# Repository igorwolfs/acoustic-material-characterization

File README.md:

# acoustic-emissions-hw
Repository for my non-destructive mechanical measurement device.

## Project Goal
Being able to measure cracks and holes in welds and solid materials by measuring mechanical wave behavior in the material.

## Description
The project will consist of 3 boards
- acoustic-processing-hw (The compute-module)
- acoustic-preamp-hw (The preamp-module)
- acoustic-piezodriver-hw (The driver-module)

## The electronics demistified

The **compute**-module will drive a PWM signal to the **driver**-module. The **driver** contains various DC-DC converters, along with a single-phase inverter. 

The inverter-output is connected to a piezo-element, driving the piezo-element with a 0.1 MHz - 10 MHz block-wave at an amplitude of 40 V, and currents up to 3 A RMS. Optional piezo-specific band-pass filters might be integrated.

The "transmitting" piezo-element and "receiving" piezo-element are connected to the **preamp** board, capable of
- Measuring transmitted power through the sending piezo.
- Measuring reflections back into the sending piezo (due to e.g.: mechanical impedance discontinuities between sending and receiving piezo).
- Measuring received power at the receiving piezo.

The **preamp** board will likely be covering only part of the 0.1-10 MHz frequency band. After some active filtering on the **preamp**-board, the signal is passed onto the front-end present on the **processing**-board. The **processing** board buffers the signal coming from the **preamp** and samples it with 10-bit accuracy at maximum 35 MHz.

## The mechanics demistified
#### Initial piezo-choice
The initial test-piezo used is the [UB161M7](https://www.mouser.de/datasheet/2/334/UB161M7-953231.pdf), which has a resonance frequency of 1.70 MHz.

#### Isotropic behavior
In order to get the best possible results, in terms of wave propagation insights and material properties. Ideally isotropic materials are used. Anisotropic materials will likely require lots of calibration and specific digital processing.

#### Piezo resonance frequency
In order to pass on vibration from the piezo onto the material, it's imperative to match their acoustic impedances. This will likely dampen the resonance curve, and shift the resonance frequency of the piezo.

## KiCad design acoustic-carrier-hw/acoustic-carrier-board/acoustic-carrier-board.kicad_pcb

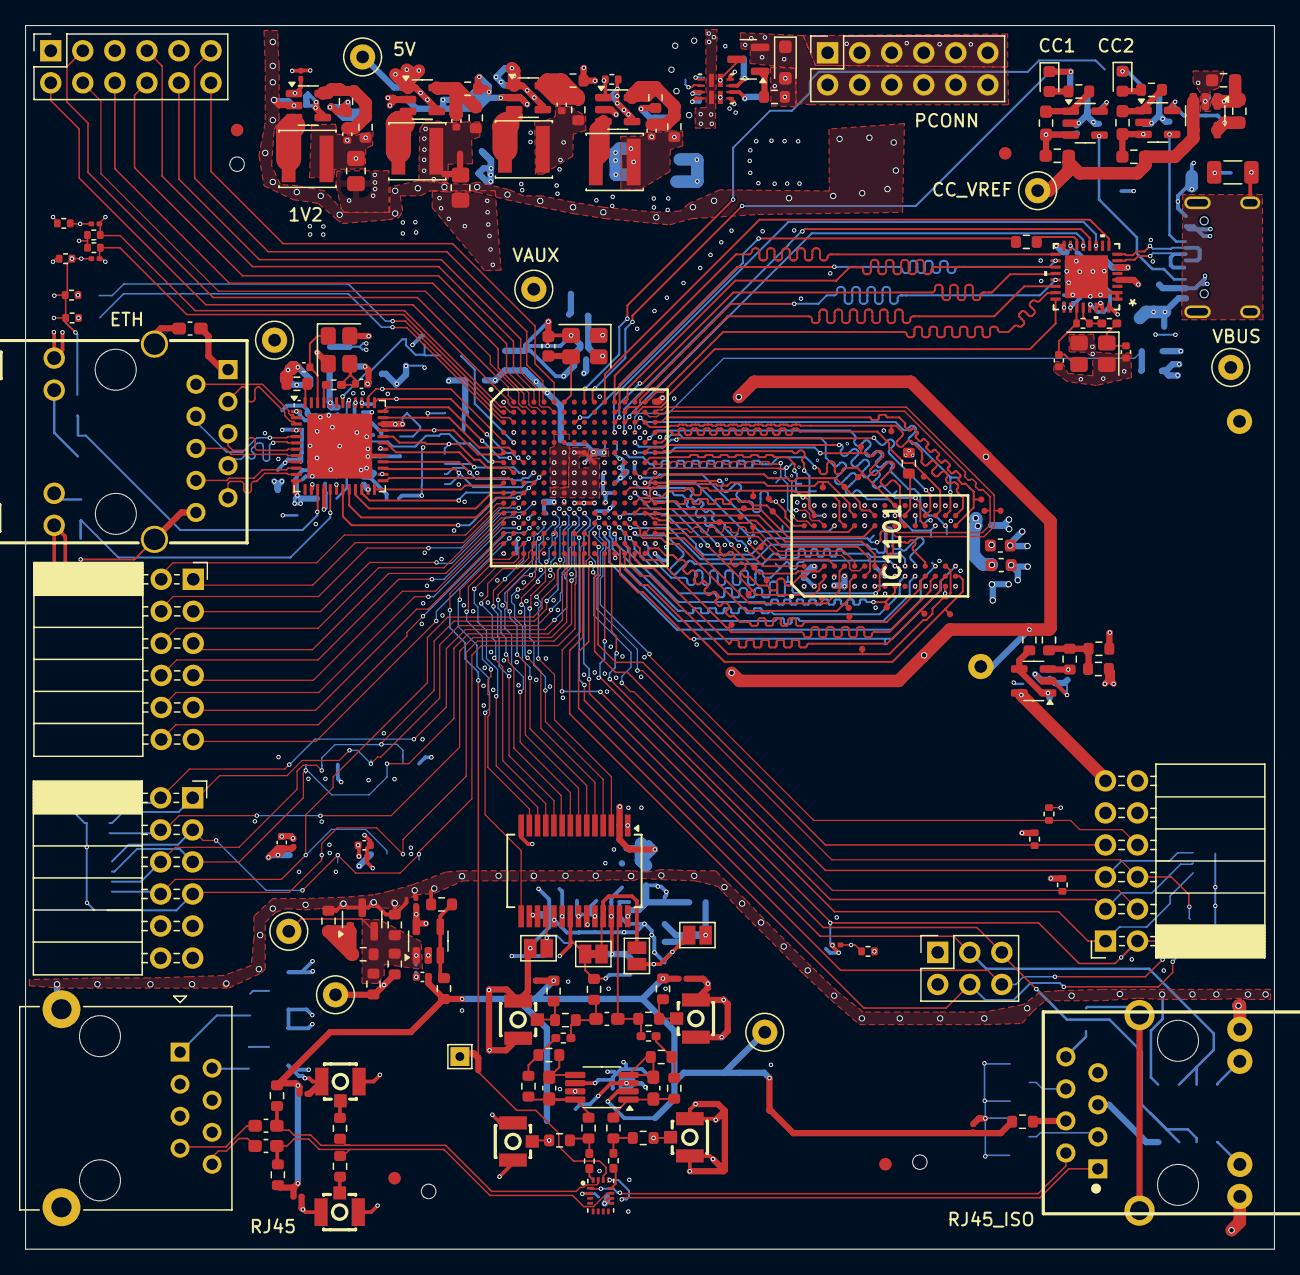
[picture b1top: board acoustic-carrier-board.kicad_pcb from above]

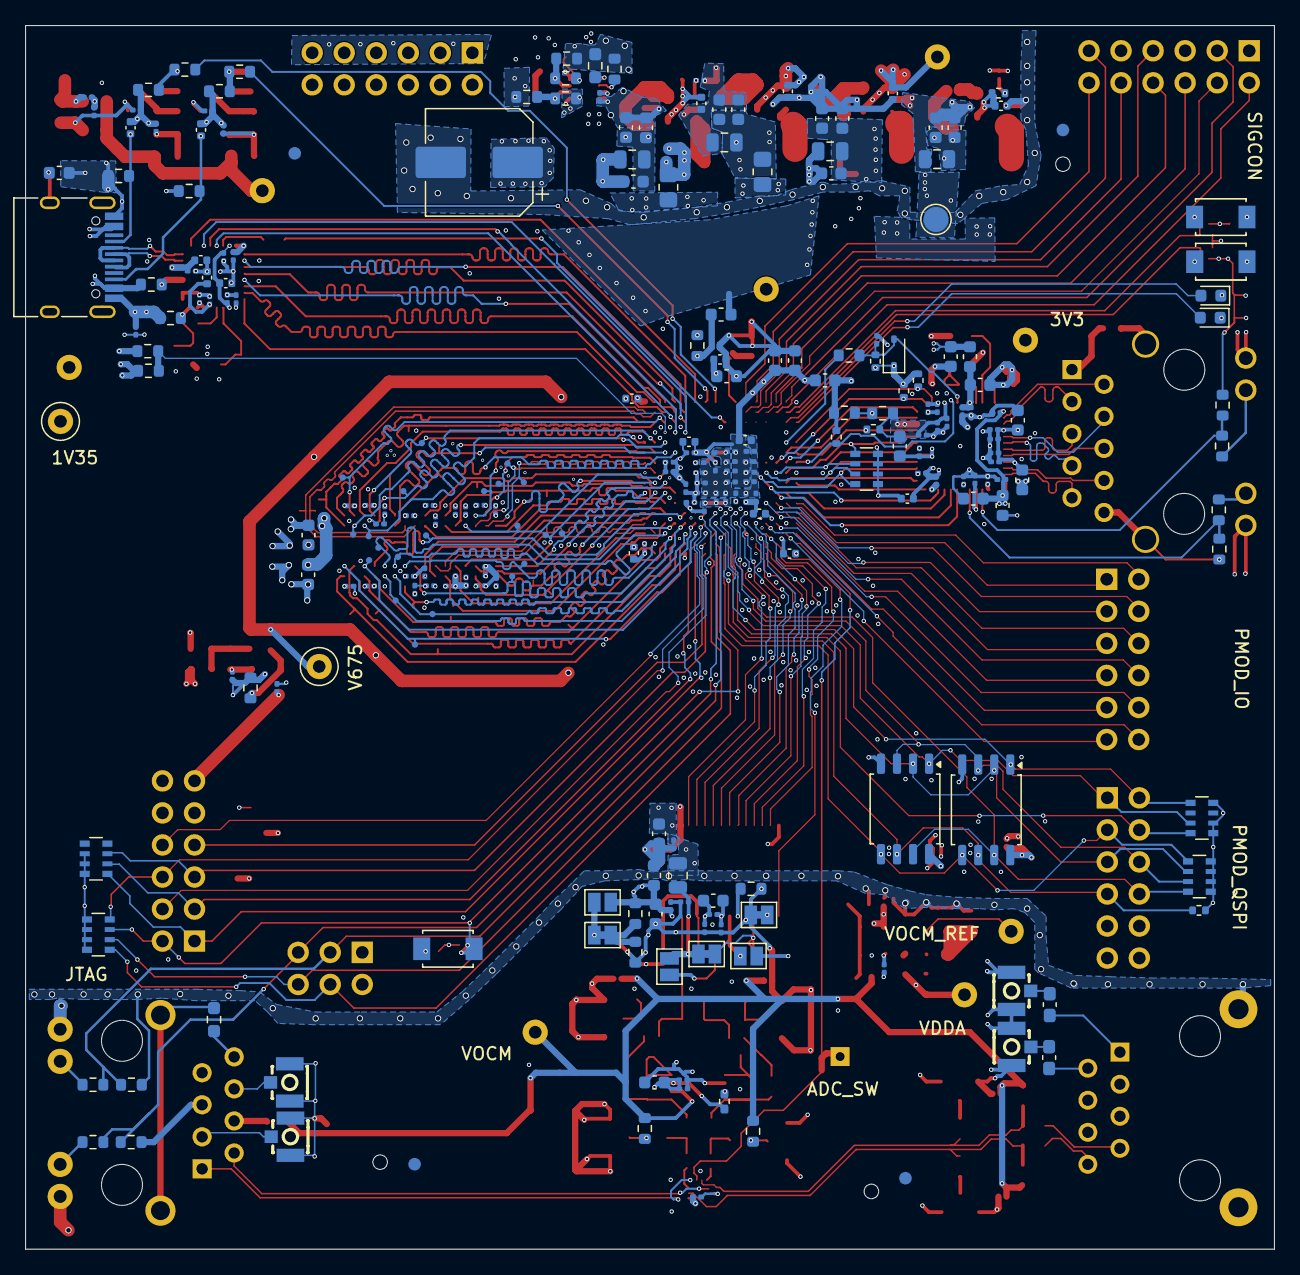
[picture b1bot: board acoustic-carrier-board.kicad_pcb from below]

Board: 6 copper layers, 99.0 x 97.0 mm, 445 parts (250 on the bottom side), 278 nets.

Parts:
C201: 150uF; CP_Elec_8x6.2
C202, C225, C227, C228, C301, C302, C303, C304, C305, C306, C310, C311, C401, C402, C404, C405, C407, C501, C502, C508, C509, C510, C513, C601, C604, C606, C612, C613, C702, C704, C706, C708, C801, C807, C808, C809, C810, C811, C812, C816, C820, C821, C822, C1002, C1003, C1004, C1005, C1008, C1009, C1010, C1011, C1013, C1019, C1021, C1024, C1026, C1027, C1101, C1102, C1103, C1104, C1105, C1106, C1108, C1109, C1110, C1111, C1112, C1116, C1118, C1119, C1120, C1121, C1122, C1123, C1124, C1125, C1203, C1204, C1206, C1207, C1209, C1210, C1216, C1217, C1218, C1219, C1220, C1221, C1222, C1223, C1229: 0.1uF; C_0201_0603Metric
C203, C209, C217, C219: 10pF; C_0402_1005Metric
C204, C205, C206, C210, C211, C214, C215, C220, C221, C222, C307, C308, C309, C1001, C1006, C1007, C1023, C1202, C1205, C1208, C1215, C1224: 10uF; C_0603_1608Metric
C207, C212, C216, C223, C1014: 1uF; C_0805_2012Metric
C208, C213, C218, C224, C312, C403, C406, C503, C512, C603, C611, C701, C705, C707, C813, C814, C819: 4.7uF; C_0402_1005Metric
C226, C507, C511, C602, C703, C802, C817, C825, C1022, C1025, C1114, C1115, C1211, C1212, C1213, C1214, C1225: 10nF; C_0201_0603Metric
C313, C1107, C1113: 22uF; C_0603_1608Metric
C408: 5pF; C_0603_1608Metric
C803, C806, C1227, C1228: 22pF; C_0402_1005Metric
C804, C805: 220pF; C_0402_1005Metric
C815: 1nF; C_1206_3216Metric
C1012, C1015, C1016: 10pF; C_0603_1608Metric_Pad1.08x0.95mm_HandSolder
C1017, C1018, C1028, C1029, C1226: 100 nF +-5%; C_0603_1608Metric_Pad1.08x0.95mm_HandSolder
C1020: 220nF; C_0402_1005Metric
D201: D_Zener; D_SOD-323_HandSoldering
D601, D602, D801, D802: LED_RED; LED_0603_1608Metric
D1201: 1N4148WS; D_SOD-323
FID101, FID102, FID103, FID104, FID105, FID106, FID107, FID108: Fiducial; Fiducial_1mm_Mask2mm
H101, H102, H103: MountingHole; ToolingHole_1.152mm
IC1: ECP5-BGA256; BGA256C80P16X16_1400X1400X170
IC1101: MT41K256M16TW-107_P; BGA96C80P9X16_800X1400X120
J201, J903: Conn_02x06_Odd_Even; PinSocket_2x06_P2.54mm_Vertical
J701: Conn_02x03_Odd_Even; PinSocket_2x03_P2.54mm_Vertical
J702: PMOD_JTAG; PMOD_Pinsocket
J703: PMOD_SPI; PMOD_Pinsocket
J704: PMOD_GPIO; PMOD_Pinsocket
J801: TYPE-C-31-M-12; USB_C_Receptacle_HRO_TYPE-C-31-M-12
J1001, J1002, J1003, J1004, J1005, J1006, J1008, J1009, J1010, J1011: BWU.FL-IPEX1
J1007: 8P8C_Shielded; RJ45_RCH_RC01937
J1201: HR911130A; RJ45-TH_HR911130A
JP1001, JP1004, JP1007, JP1008: SolderJumper_2_Bridged; SolderJumper-2_P1.3mm_Bridged_Pad1.0x1.5mm
JP1002, JP1003, JP1005, JP1006, JP1009, JP1010: SolderJumper_2_Open; SolderJumper-2_P1.3mm_Open_Pad1.0x1.5mm
L201, L202, L203, L204: 2.2uH; L_Changjiang_FNR4018S
L401, L801, L1001, L1101, L1102, L1201, L1202, L1203: 120@100MHz; L_0603_1608Metric
Q201: AO3401A; SOT-23
R201, R202, R604, R606, R704, R705, R707, R1204, R1208, R1212, R1213: 4.7k; R_0402_1005Metric
R203, R216, R225, R226: 24k; R_0603_1608Metric
R204, R803, R811: 100k; R_0603_1608Metric_Pad0.98x0.95mm_HandSolder
R205: 27k; R_0603_1608Metric
R206, R212: 22k; R_0603_1608Metric
R207, R227, R804, R805: 5.1k; R_0603_1608Metric
R208, R209, R217, R301: 0; R_0805_2012Metric_Pad1.20x1.40mm_HandSolder
R210, R211, R213: 100k; R_0603_1608Metric
R215: 75k; R_0603_1608Metric
R218: 30k; R_0603_1608Metric
R219, R223, R224, R401, R815, R830, R1009, R1013, R1021, R1024, R1030, R1031, R1032, R1034, R1036, R1037: 1k; R_0603_1608Metric
R220, R221, R602, R817, R1007, R1008, R1011, R1014, R1022, R1025, R1026, R1039, R1043: 0; R_0603_1608Metric
R222, R801: 220; R_0603_1608Metric
R601, R603, R605, R607, R701: 470; R_0402_1005Metric
R706, R1205: 1k; R_0402_1005Metric
R802, R812: 3k9; R_0603_1608Metric_Pad0.98x0.95mm_HandSolder
R806: 1M; R_0402_1005Metric
R807, R1012, R1015, R1017, R1018, R1020, R1201: 0; R_0402_1005Metric_Pad0.72x0.64mm_HandSolder
R808, R1202: 12k+-1%; R_0603_1608Metric
R809, R810: 33k; R_0603_1608Metric
R813, R821, R1016, R1019: 47; R_0603_1608Metric
R814, R826, R1038: 4.7k; R_0603_1608Metric
R816: 56k; R_0603_1608Metric_Pad0.98x0.95mm_HandSolder
R818: 9k1; R_0603_1608Metric_Pad0.98x0.95mm_HandSolder
R1001: 0; R_0603_1608Metric_Pad0.98x0.95mm_HandSolder
R1002, R1003, R1004, R1005, R1206, R1209: 470; R_0603_1608Metric
R1006, R1010, R1023, R1027, R1028, R1029, R1203, R1207, R1210, R1211: 10k; R_0603_1608Metric
R1033: 75; R_0603_1608Metric
R1035: 1k5; R_0603_1608Metric
R1101: 240; R_0603_1608Metric
RJ1001: HR913550A; RJ45-TH_HR913550A
RN703, RN704, RN708, RN1201: 4x4k7; R_Array_Convex_4x0603
RN707: 4x10k; R_Array_Convex_4x0603
SW602, SW603, SW701: SW_Push; SW_TS-1088-AR02016
TP202, TP205, TP207, TP208, TP209, TP210, TP801, TP1001, TP1011, TP1012: TestPoint; TestPoint_Loop_D1.80mm_Drill1.0mm_Beaded
TP206: TestPoint; TestPoint_Pad_D2.0mm
TP1005: TestPoint; TestPoint_THTPad_1.5x1.5mm_Drill0.7mm
TP1101, TP1102, TP1103, TP1104, TP1105, TP1106, TP1107, TP1108, TP1109, TP1110, TP1111, TP1112, TP1113, TP1114, TP1115, TP1116, TP1117, TP1118, TP1119, TP1120, TP1121, TP1122, TP1123, TP1124, TP1125, TP1126, TP1127, TP1128, TP1129, TP1130, TP1131, TP1132, TP1133, TP1134, TP1135, TP1136, TP1137, TP1138, TP1139, TP1140, TP1141, TP1142, TP1143, TP1144, TP1145, TP1146, TP1147, TP1148, TP1149: TestPoint_0.25mm; TestPoint_Pad_D0.25mm
U201: TPS2121RUX; TPS2121
U202, U203, U204, U205: TLV62569DBV; SOT-23-5
U206: OPA376xxDBV; SOT-23-5
U701, U702: W25Q128JVS; SOIC-8_5.3x5.3mm_P1.27mm
U801: USB3300-EZK; QFN32_5X5MC_MCH
U802, U1004: LMV321; SOT-23-5
U803, U804: SOT-23-5
U1001: MS9280; SSOP-28_5.3x10.2mm_P0.65mm
U1002: THS4521IDGK; VSSOP-8_3x3mm_P0.65mm
U1003: DGQ2788AEN-T1-GE4; QFN40P260X180X60-16N_Fv1.2
U1005: TL432DBZ; SOT-23
U1201: KSZ9031RN; QFN-48-1EP_7x7mm_P0.5mm_EP5.15x5.15mm
Y401: Crystal Oscillator; Crystal_SMD_3225-4Pin_3.2x2.5mm
Y801: Crystal_GND24_Small; Crystal_SMD_3225-4Pin_3.2x2.5mm
Y1201: 25MHz; Crystal_SMD_3225-4Pin_3.2x2.5mm

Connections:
+1V2: C209.1, C210.1, C211.1, C212.1, L202.2, R209.1, R211.2
+1V35: C219.1, C220.1, C221.1, C222.1, C223.1, L204.2, R217.1, R218.2
+2V5: C214.1, C215.1, C216.1, C217.1, L203.2, R215.2, R301.1
+3V3: C203.1, C204.1, C205.1, C206.1, C207.1, L201.2, R208.1, R210.2
+5V: C201.1, C208.1, C213.1, C218.1, C224.1, R201.1, R202.1, TP202.1, U201.1 (OUT), U201.8 (OUT), U202.1 (EN), U202.4 (VIN), U203.4 (VIN), U204.1 (EN), U204.4 (VIN), U205.4 (VIN)
/ANALOG-FRONTEND/ADC.CLK: IC1.T2 (PL38D), U1001.15 (CLK)
/ANALOG-FRONTEND/ADC.D0: IC1.M6 (PL47A), U1001.3 (D0)
/ANALOG-FRONTEND/ADC.D1: IC1.P6 (PL47C/LLC_GPLL0T_IN), U1001.4 (D1)
/ANALOG-FRONTEND/ADC.D2: IC1.N6 (PL47B), U1001.5 (D2)
/ANALOG-FRONTEND/ADC.D3: IC1.R5 (PL44A/LDQS44), U1001.6 (D3)
/ANALOG-FRONTEND/ADC.D4: IC1.P5 (PL47D/LLC_GPLL0C_IN), U1001.7 (D4)
/ANALOG-FRONTEND/ADC.D5: IC1.N5 (PL44D), U1001.8 (D5)
/ANALOG-FRONTEND/ADC.D6: IC1.T4 (PL44B/LDQSN44), U1001.9 (D6)
/ANALOG-FRONTEND/ADC.D7: IC1.P4 (PL41A), U1001.10 (D7)
/ANALOG-FRONTEND/ADC.D8: IC1.R4 (PL41C), U1001.11 (D8)
/ANALOG-FRONTEND/ADC.D9: IC1.T3 (PL41D), U1001.12 (D9)
/ANALOG-FRONTEND/ADC.OTR: IC1.R3 (PL41B), U1001.13 (OTR)
/ANALOG-FRONTEND/ADC_AIN+: C1015.2, R1011.1, R1017.2, U1001.27 (AIN)
/ANALOG-FRONTEND/ADC_AIN-: C1015.1, R1014.1, R1020.2, R1022.1
/ANALOG-FRONTEND/ADC_MODE: JP1006.2 (B), JP1008.2 (B), JP1010.2 (B), U1001.23 (MODE)
/ANALOG-FRONTEND/ADC_REFBF: C1001.2, C1002.2, C1004.1, U1001.24 (REFBF)
/ANALOG-FRONTEND/ADC_REFBS: JP1004.1 (A), JP1005.2 (B), U1001.25 (REFBS)
/ANALOG-FRONTEND/ADC_REFSENSE: JP1007.2 (B), JP1009.2 (B), U1001.18 (REFSENSE)
/ANALOG-FRONTEND/ADC_REFTF: C1001.1, C1002.1, C1003.1, U1001.22 (REFTF)
/ANALOG-FRONTEND/ADC_REFTS: JP1002.2 (B), JP1003.2 (B), JP1004.2 (B), R1014.2, U1001.21 (REFTS)
/ANALOG-FRONTEND/ADC_VDDA_2: JP1008.1 (A), R1030.2, R1031.1
/ANALOG-FRONTEND/ADC_VOCM_BUFF: C1009.1, C1010.1, C1011.1, C1020.2, C1026.1, C1027.1, R1006.1, R1010.1, R1023.1, R1027.1, R1028.1, R1029.2, R1033.1, R1039.1, TP1012.1, U1002.2 (V_{OCM})
/ANALOG-FRONTEND/ADC_VOCM_REF: C1022.1, R1032.2, R1034.2, R1035.1, R1037.1, TP1011.1, U1004.1 (+), U1005.2 (K)
/ANALOG-FRONTEND/ADC_VREF: C1013.1, C1014.1, JP1002.1 (A), JP1007.1 (A), U1001.26 (VREF)
/ANALOG-FRONTEND/MAG_ADC_AIN+: RJ1001.2, U1003.1 (NC2)
/ANALOG-FRONTEND/MAG_ADC_AIN-: RJ1001.1, U1003.13 (NC1)
/ANALOG-FRONTEND/RJ45_ADC_AIN+: C1018.2, R1008.1, R1029.1, U1003.15 (NO2)
/ANALOG-FRONTEND/RJ45_ADC_AIN-: C1017.2, R1027.2, R1043.1, U1003.11 (NO1)
/CONNECTORS/PMOD_IO.IO1: IC1.L2 (PL26B/PCLKC6_1), J704.1 (IO1/TMS)
/CONNECTORS/PMOD_IO.IO2: IC1.L4 (PL29C/PL29C), J704.2 (IO2/TDI)
/CONNECTORS/PMOD_IO.IO3: IC1.M2 (PL26D/PCLKC6_0), J704.3 (IO3/TDO)
/CONNECTORS/PMOD_IO.IO4: IC1.N1 (PL32A/LDQS32), J704.4 (IO4/TCK)
/CONNECTORS/PMOD_IO.IO5: IC1.P1 (PL35A), J704.5 (GND)
/CONNECTORS/PMOD_IO.IO6: IC1.P2 (PL32B/LDQSN32), J704.6 (Vcc)
/CONNECTORS/PMOD_IO.IO7: IC1.L1 (PL26A/LDQ32/PCLKT6_1), J704.7 (IO5)
/CONNECTORS/PMOD_IO.IO8: IC1.L3 (PL32C), J704.8 (IO6)
/CONNECTORS/PMOD_IO.IO9: IC1.M1 (PL26C/PCLKT6_0), J704.9 (IO7)
/CONNECTORS/PMOD_IO.IO10: IC1.M3 (PL32D), J704.10 (IO8)
/CONNECTORS/PMOD_IO.IO11: IC1.N3 (PL35D), J704.11 (GND)
/CONNECTORS/PMOD_IO.IO12: IC1.N4 (PL38A/LDQ44), J704.12 (Vcc)
/CONNECTORS/SIGCON.IO1: IC1.B3 (PT4B), J903.2
/CONNECTORS/SIGCON.IO2: IC1.A2 (PT4A), J903.3
/CONNECTORS/SIGCON.IO3: IC1.B4 (PT11B), J903.4
/CONNECTORS/SIGCON.IO4: IC1.A3 (PT6A), J903.6
/CONNECTORS/SIGCON.IO5: IC1.A4 (PT6B), J903.7
/CONNECTORS/SIGCON.IO6: IC1.B5 (PT15B), J903.8
/CONNECTORS/SIGCON.IO7: IC1.B6 (PT22B), J903.10
/CONNECTORS/SIGCON.IO8: IC1.A5 (PT18A), J903.11
/CONNECTORS/SIGCON.IO9: IC1.A6 (PT18B), J903.12
/DDR3/DDR3.A0: IC1.M12 (PR44C), IC1101.N3 (A0), TP1137.1
/DDR3/DDR3.A1: IC1.E16 (PR11D/RDQ8), IC1101.P7 (A1), TP1136.1
/DDR3/DDR3.A2: IC1.P11 (PR47C/LRC_GPLL0T_IN), IC1101.P3 (A2), TP1135.1
/DDR3/DDR3.A3: IC1.T15 (PR38D), IC1101.N2 (A3), TP1134.1
/DDR3/DDR3.A4: IC1.D16 (PR8A/RDQS8), IC1101.P8 (A4), TP1133.1
/DDR3/DDR3.A5: IC1.R14 (PR41B), IC1101.P2 (A5), TP1132.1
/DDR3/DDR3.A6: IC1.C14 (PR2C), IC1101.R8 (A6), TP1131.1
/DDR3/DDR3.A7: IC1.T14 (PR41D), IC1101.R2 (A7), TP1130.1
/DDR3/DDR3.A8: IC1.C15 (PR5B), IC1101.T8 (A8), TP1129.1
/DDR3/DDR3.A9: IC1.R13 (PR41C), IC1101.R3 (A9), TP1128.1
/DDR3/DDR3.A10: IC1.F14 (PR5D), IC1101.L7 (A10/AP), TP1127.1
/DDR3/DDR3.A11: IC1.E15 (PR8B/RDQSN8), IC1101.R7 (A11), TP1126.1
/DDR3/DDR3.A12: IC1.F15 (PR11C), IC1101.N7 (A12/BC#), TP1125.1
/DDR3/DDR3.A13: IC1.R12 (PR44A/RDQS44), IC1101.T3 (A13), TP1102.1
/DDR3/DDR3.A14: IC1.C16 (PR5A), IC1101.T7 (A14), TP1101.1
/DDR3/DDR3.BA0: IC1.N11 (PR47B), IC1101.M2 (BA0), TP1146.1
/DDR3/DDR3.BA1: IC1.E14 (PR5C), IC1101.N8 (BA1), TP1147.1
/DDR3/DDR3.BA2: IC1.N13 (PR38A/RDQ44), IC1101.M3 (BA2), TP1148.1
/DDR3/DDR3.CAS#: IC1.R15 (PR38C), IC1101.K3 (CAS#), TP1145.1
/DDR3/DDR3.CK+: IC1.B16 (PR2A/RDQ8), IC1101.J7 (CK), TP1143.1
/DDR3/DDR3.CK-: IC1.B15 (PR2B/S0_IN), IC1101.K7 (CK#), TP1142.1
/DDR3/DDR3.CKE: IC1.F13 (PR8C), IC1101.K9 (CKE), TP1149.1
/DDR3/DDR3.CS#: IC1.P12 (PR47D/LRC_GPLL0C_IN/RDQ44), IC1101.L2 (CS#), TP1140.1
/DDR3/DDR3.DQ0: IC1.P16 (PR35A), IC1101.E3 (DQ0), TP1103.1
/DDR3/DDR3.DQ1: IC1.L16 (PR26A/PCLKT3_1/RDQ32), IC1101.F7 (DQ1), TP1106.1
/DDR3/DDR3.DQ2: IC1.N14 (PR35D/RDQ32), IC1101.F2 (DQ2), TP1116.1
/DDR3/DDR3.DQ3: IC1.L14 (PR32C), IC1101.F8 (DQ3), TP1117.1
/DDR3/DDR3.DQ4: IC1.M16 (PR26C/PCLKT3_0), IC1101.H3 (DQ4), TP1118.1
/DDR3/DDR3.DQ5: IC1.K13 (PR29A/GR_PCLK3_0), IC1101.H8 (DQ5), TP1119.1
/DDR3/DDR3.DQ6: IC1.M15 (PR26D/PCLKC3_0), IC1101.G2 (DQ6), TP1120.1
/DDR3/DDR3.DQ7: IC1.M14 (PR32D), IC1101.H7 (DQ7), TP1121.1
/DDR3/DDR3.DQ8: IC1.H14 (PR14D), IC1101.D7 (DQ8), TP1114.1
/DDR3/DDR3.DQ9: IC1.K16 (PR23C/PCLKT2_0), IC1101.C3 (DQ9), TP1113.1
/DDR3/DDR3.DQ10: IC1.F16 (PR14A/RDQ20), IC1101.C8 (DQ10), TP1112.1
/DDR3/DDR3.DQ11: IC1.K14 (PR20D/GR_PCLK2_0), IC1101.C2 (DQ11), TP1111.1
/DDR3/DDR3.DQ12: IC1.J16 (PR23A/PCLKT2_1), IC1101.A7 (DQ12), TP1110.1
/DDR3/DDR3.DQ13: IC1.K15 (PR23D/PCLKC2_0/RDQ20), IC1101.A2 (DQ13), TP1115.1
/DDR3/DDR3.DQ14: IC1.G15 (PR14B), IC1101.B8 (DQ14), TP1109.1
/DDR3/DDR3.DQ15: IC1.J14 (PR20C/GR_PCLK2_1), IC1101.A3 (DQ15), TP1108.1
/DDR3/DDR3.LDM: IC1.L15 (PR26B/PCLKC3_1), IC1101.E7 (LDM), TP1124.1
/DDR3/DDR3.LDQS+: IC1.N16 (PR32A/RDQS32), IC1101.F3 (LDQS), TP1123.1
/DDR3/DDR3.LDQS-: IC1.P15 (PR32B/RDQSN32), IC1101.G3 (LDQS#), TP1122.1
/DDR3/DDR3.ODT: IC1.N12 (PR44D), IC1101.K1 (ODT), TP1141.1
/DDR3/DDR3.RAS#: IC1.P13 (PR41A), IC1101.J3 (RAS#), TP1144.1
/DDR3/DDR3.RESET#: IC1.T13 (PR44B/RDQSN44), IC1101.T2 (RESET#), TP1138.1
/DDR3/DDR3.UDM: IC1.J15 (PR23B/PCLKC2_1), IC1101.D3 (UDM), TP1104.1
/DDR3/DDR3.UDQS+: IC1.G16 (PR20A/RDQS20), IC1101.B7 (UDQS#), TP1105.1
/DDR3/DDR3.UDQS-: IC1.H15 (PR20B/RDQSN20), IC1101.C7 (UDQS), TP1107.1
/DDR3/DDR3.WE#: IC1.P14 (PR38B), IC1101.L3 (WE#), TP1139.1
/DDR3/VLPDDR3_CORE: C1101.1, C1103.1, C1104.1, C1105.1, C1106.1, C1107.1, C1118.1, C1119.1, C1120.1, C1124.1, IC1101.B2 (VDD_1), IC1101.D9 (VDD_2), IC1101.G7 (VDD_3), IC1101.K2 (VDD_4), IC1101.K8 (VDD_5), IC1101.N1 (VDD_6), IC1101.N9 (VDD_7), IC1101.R1 (VDD_8), IC1101.R9 (VDD_9), L1101.1
/DDR3/VLPDDR3_DQ: C1102.1, C1108.1, C1109.1, C1110.1, C1111.1, C1112.1, C1113.1, C1116.1, C1123.1, C1125.1, IC1101.A1 (VDDQ_1), IC1101.A8 (VDDQ_2), IC1101.C1 (VDDQ_3), IC1101.C9 (VDDQ_4), IC1101.D2 (VDDQ_5), IC1101.E9 (VDDQ_6), IC1101.F1 (VDDQ_7), IC1101.H2 (VDDQ_8), IC1101.H9 (VDDQ_9), L1102.1
/ETHERNET-PHY/ETH_AC_GND: C1226.1, J1201.1
/ETHERNET-PHY/ETH_GLED_K: J1201.12, R1206.1
/ETHERNET-PHY/ETH_LED_1: R1209.2, R1210.1, U1201.17 (LED1/PHAD0/PME_N1)
/ETHERNET-PHY/ETH_LED_2: R1206.2, R1207.1, U1201.15 (LED2/PHYAD1)
/ETHERNET-PHY/ETH_PHY_A+: J1201.2, U1201.2 (TXRXP_A)
/ETHERNET-PHY/ETH_PHY_A-: J1201.3, U1201.3 (TXRXM_A)
/ETHERNET-PHY/ETH_PHY_B+: J1201.4, U1201.5 (TXRXP_B)
/ETHERNET-PHY/ETH_PHY_B-: J1201.7, U1201.6 (TXRXM_B)
/ETHERNET-PHY/ETH_PHY_C+: J1201.5, U1201.7 (TXRXP_C)
/ETHERNET-PHY/ETH_PHY_C-: J1201.6, U1201.8 (TXRXM_C)
/ETHERNET-PHY/ETH_PHY_D+: J1201.8, U1201.10 (TXRXP_D)
/ETHERNET-PHY/ETH_PHY_D-: J1201.9, U1201.11 (TXRXM_D)
/ETHERNET-PHY/ETH_YLED_K: J1201.13, R1209.1
/ETHERNET-PHY/RGMII_MDIO.CLK: IC1.G2 (PL14B), U1201.36 (MDC)
/ETHERNET-PHY/RGMII_MDIO.DATA: IC1.G3 (PL14C), R1205.1, U1201.37 (MDIO)
/ETHERNET-PHY/RGMII_RX.CLK: IC1.F2 (PL11C), R1203.2, R1211.1, U1201.35 (RX_CLK/PHYAD2)
/ETHERNET-PHY/RGMII_RX.CTL: IC1.F1 (PL14A/LDQ20), R1204.1, U1201.33 (RX_DV/CLK125_EN)
/ETHERNET-PHY/RGMII_RX.D0: IC1.H2 (PL20B/LDQS20), RN1201.1 (R1.1), U1201.32 (RXD0/MODE0)
/ETHERNET-PHY/RGMII_RX.D1: IC1.H3 (PL14D), RN1201.2 (R2.1), U1201.31 (RXD1/MODE1)
/ETHERNET-PHY/RGMII_RX.D2: IC1.H4 (PL17B), RN1201.3 (R3.1), U1201.28 (RXD2/MODE2)
/ETHERNET-PHY/RGMII_RX.D3: IC1.H5 (PL17A), RN1201.4 (R4.1), U1201.27 (RXD3/MODE3)
/ETHERNET-PHY/RGMII_TX.CLK: IC1.J1 (PL23A/PCLKT7_1), U1201.24 (GTX_CLK)
/ETHERNET-PHY/RGMII_TX.CTL: IC1.J2 (PL23B/PCLKC7_1), U1201.25 (TX_EN)
/ETHERNET-PHY/RGMII_TX.D0: IC1.K3 (PL20D), U1201.19 (TXD0)
/ETHERNET-PHY/RGMII_TX.D1: IC1.K2 (PL23D/PCLKC7_0/LDQ20), U1201.20 (TXD1)
/ETHERNET-PHY/RGMII_TX.D2: IC1.K1 (PL23C/PCLKT7_0), U1201.21 (TXD2)
/ETHERNET-PHY/RGMII_TX.D3: IC1.J4 (PL17C), U1201.22 (TXD3)
/ETHERNET-PHY/VDDAH_3V3: C1202.1, C1203.1, C1204.1, L1203.2, U1201.1 (AVDDH), U1201.12 (AVDDH)
/ETHERNET-PHY/VDDAL_1V2: C1208.1, C1209.1, C1210.1, C1211.1, C1212.1, L1201.1, U1201.4 (AVDDL), U1201.9 (AVDDL)
/ETHERNET-PHY/VDDAPLL_1V2: C1205.1, C1206.1, C1207.1, L1202.1, U1201.44 (AVDDL_PLL)
/FPGA-BANK-01/USB.CLK: IC1.C8 (PT35A/PCLKT1_0), R817.2
/FPGA-BANK-01/USB.D0: IC1.B14 (PT67A), U801.24 (DATA0)
/FPGA-BANK-01/USB.D1: IC1.A15 (PT67B), U801.23 (DATA1)
/FPGA-BANK-01/USB.D2: IC1.B13 (PT60A), U801.22 (DATA2)
/FPGA-BANK-01/USB.D3: IC1.A14 (PT65B), U801.21 (DATA3)
/FPGA-BANK-01/USB.D4: IC1.C12 (PT56B), U801.20 (DATA4)
/FPGA-BANK-01/USB.D5: IC1.A13 (PT65A), U801.19 (DATA5)
/FPGA-BANK-01/USB.D6: IC1.B12 (PT56A), U801.18 (DATA6)
/FPGA-BANK-01/USB.D7: IC1.A12 (PT53B), U801.17 (DATA7)
/FPGA-BANK-01/USB.DIR: IC1.D13 (PT62A), U801.12 (DIR)
/FPGA-BANK-01/USB.NXT: IC1.D12 (PT58A), U801.11 (NXT)
/FPGA-BANK-01/USB.RST: IC1.A11 (PT53A), U801.9 (RESET)
/FPGA-BANK-01/USB.STP: IC1.C13 (PT60B), U801.13 (STP)
/FPGA-CONFIG-FLASH/FPGA_CFG0: IC1.N10 (CFG0), J702.10 (IO8), R705.1
/FPGA-CONFIG-FLASH/FPGA_CFG1: IC1.P10 (CFG1), J702.9 (IO7), RN704.4 (R4.1)
/FPGA-CONFIG-FLASH/FPGA_CFG2: IC1.R10 (CFG2), J702.8 (IO6), R707.2
/FPGA-CONFIG-FLASH/FPGA_DONE: IC1.P9 (DONE), J701.6, RN704.2 (R2.1)
/FPGA-CONFIG-FLASH/FPGA_RESETH: C708.1, IC1.R9 (~PROGRAM), J702.7 (IO5), RN704.3 (R3.1), SW701.1
/FPGA-CONFIG-FLASH/JTAG.TCK: IC1.T10 (TCK), J702.4 (IO4/TCK), R704.1
/FPGA-CONFIG-FLASH/JTAG.TDI: IC1.R11 (TDI), J702.2 (IO2/TDI), RN703.2 (R2.1)
/FPGA-CONFIG-FLASH/JTAG.TDO: IC1.M10 (TDO), J702.3 (IO3/TDO), RN703.3 (R3.1)
/FPGA-CONFIG-FLASH/JTAG.TMS: IC1.T11 (TMS), J702.1 (IO1/TMS), RN703.1 (R1.1)
/FPGA-CONFIG-FLASH/QSPI.CSPPIn1: IC1.N8 (~HOLD/DI/BUSY/~CSSPI/PB15A), J703.1 (CSn), RN708.3 (R3.1), U701.1 (~CS)
/FPGA-CONFIG-FLASH/QSPI.CSPPIn2: IC1.M8 (DOUT/~CSO/PB15B), J703.7 (IO1), RN708.1 (R1.1), U702.1 (~CS)
/FPGA-CONFIG-FLASH/QSPI.CSn: IC1.R8 (~CS/~S/PB13A), J703.8 (IO2), RN708.4 (R4.1)
/FPGA-CONFIG-FLASH/QSPI.D0: IC1.T8 (D0/PICO/IO0/PB11B), J703.2 (MOSI/DQ0), RN707.1 (R1.1), U701.5 (DI/IO_{0}), U702.5 (DI/IO_{0})
/FPGA-CONFIG-FLASH/QSPI.D1: IC1.T7 (D1/POCI/IO1/PB11A), J703.3 (MISO/DQ1), RN707.2 (R2.1), U701.2 (DO/IO_{1}), U702.2 (DO/IO_{1})
/FPGA-CONFIG-FLASH/QSPI.D2: IC1.M7 (D2/IO2/PB9B), J703.9 (W/DQ2), RN707.3 (R3.1), U701.3 (~WP/IO_{2}), U702.3 (~WP/IO_{2})
/FPGA-CONFIG-FLASH/QSPI.D3: IC1.N7 (D3/IO3/PB9A), J703.10 (HLD/DQ3), RN707.4 (R4.1), U701.7 (~HOLD/~RESET/IO_{3}), U702.7 (~HOLD/~RESET/IO_{3})
/FPGA-CONFIG-FLASH/QSPI.MCLK: IC1.N9 (MCLK/SCK/CCLK), J703.4 (SCK), R706.2, U701.6 (CLK), U702.6 (CLK)
/FPGA-CONFIG-FLASH/~FPGA_INIT: IC1.T9 (~INIT), J701.4, RN704.1 (R1.1)
/FPGA-DQBANK-67/BUTTON_1: C606.1, IC1.B2 (PL2B), R604.2, SW602.1
/FPGA-DQBANK-67/BUTTON_2: C604.1, IC1.B1 (PL2A/LDQ8), R606.2, SW603.1
/FPGA-DQBANK-67/LED_1: D602.2 (A), IC1.C1 (PL5A)
/FPGA-DQBANK-67/LED_2: D601.2 (A), IC1.C2 (PL5B)
/FPGA-POWER/VAUX: C310.1, C311.1, C312.1, C313.1, IC1.G11 (VCCAUX_1), IC1.L7 (VCCAUX_2), R301.2, TP207.1
/POWER/BP_5V: D201.1 (K), J201.2, J201.4, J201.6, J201.8, J201.10, J201.12, Q201.2 (S)
/POWER/USB_VBUS: C801.1, C807.1, C808.1, C822.1, J801.A4 (VBUS), J801.A9 (VBUS), J801.B4 (VBUS), J801.B9 (VBUS), R226.1, R801.1, R809.1, R816.2, TP210.1, U201.2 (IN2), U802.5 (V+), U803.5 (V+), U804.5 (V+)
/USB-PHY/USBCC_VREF_BUFF: R802.1, R812.1, TP801.1, U802.3 (-), U802.4
/USB-PHY/USB_CC1: C805.1, J801.A5 (CC1), R805.2, U804.4 (-)
/USB-PHY/USB_CC2: C804.1, J801.B5 (CC2), R804.2, U803.4 (-)
/USB-PHY/USB_D+: J801.A6 (DP1), J801.B6 (DP2), U801.7 (DP)
/USB-PHY/USB_D-: J801.A7 (DN1), J801.B7 (DN2), U801.8 (DM)
/USB-PHY/USB_SH: C815.1, J801.S1 (SHIELD), L801.2
/USB-PHY/VDDA_USB1V8: C814.1, C816.1, U801.29 (VDDA1.8)
/USB-PHY/VDD_USB1V8: C819.1, C820.1, C821.1, U801.15 (VDD1.8), U801.26 (VDD1.8)
ETH_REFCLK: IC1.G1 (PL20A/GR_PCLK7_1/LDQSN20), R1213.1, U1201.41 (CLK125_NDO/LED_MODE)
FPGA_ADC_LED0: IC1.M9 (~WRITE/PB18A), J701.5, R1004.2, R1005.2
FPGA_ADC_LED1: IC1.P8 (~CS1/PB13B), J701.3, R1002.2, R1003.1
FPGA_ADC_SW: IC1.R1 (PL35B/VREF1_6), TP1005.1, U1003.14 (IN1-2)
FPGA_CC1: IC1.A10 (PT42B), R814.1
FPGA_CC2: IC1.A9 (PT42A), R826.1
FPGA_USB_SENSE: IC1.D14 (PR2D), R809.2, R810.1
GND: C201.2, C202.2, C204.2, C205.2, C206.2, C207.2, C208.2, C210.2, C211.2, C212.2, C213.2, C214.2, C215.2, C216.2, C218.2, C220.2, C221.2, C222.2, C223.2, C224.2, C225.2, C226.2, C227.2, C228.2, C301.2, C302.2, C303.2, C304.2, C305.2, C306.2, C307.2, C308.2, C309.2, C310.2, C311.2, C312.2, C313.2, C401.2, C402.2, C403.2, C404.2, C405.2, C406.2, C407.2, C408.2, C501.2, C502.2, C503.2, C507.2, C508.2, C509.2, C510.2, C511.2, C512.2, C513.2, C601.2, C602.2, C603.2, C604.2, C606.2, C611.2, C612.2, C613.2, C701.2, C702.2, C703.2, C704.2, C705.2, C706.2, C707.2, C708.2, C801.2, C802.2, C803.1, C804.2, C805.2, C806.1, C807.2, C808.2, C809.2, C810.2, C811.2, C812.2, C813.2, C814.2, C815.2, C816.2, C817.2, C819.2, C820.2, C821.2, C822.2, C825.2, C1003.2, C1004.2, C1005.2, C1006.2, C1007.2, C1008.2, C1009.2, C1010.2, C1011.2, C1013.2, C1014.2, C1019.2, C1020.1, C1021.2, C1022.2, C1023.2, C1024.2, C1025.2, C1026.2, C1027.2, C1101.2, C1102.2, C1103.2, C1104.2, C1105.2, C1106.2, C1107.2, C1108.2, C1109.2, C1110.2, C1111.2, C1112.2, C1113.2, C1114.2, C1115.2, C1116.2, C1118.2, C1119.2, C1120.2, C1121.2, C1122.2, C1123.2, C1124.2, C1125.2, C1202.2, C1203.2, C1204.2, C1205.2, C1206.2, C1207.2, C1208.2, C1209.2, C1210.2, C1211.2, C1212.2, C1213.2, C1214.2, C1215.2, C1216.2, C1217.2, C1218.2, C1219.2, C1220.2, C1221.2, C1222.2, C1223.2, C1224.2, C1225.2, C1226.2, C1227.1, C1228.1, C1229.2, D201.2 (A), IC1.A1 (GND_1), IC1.A16 (GND_2), IC1.D2 (GND_3), IC1.D15 (GND_4), IC1.F8 (GND_5), IC1.F9 (GND_6), IC1.G8 (GND_7), IC1.G10 (GND_8), IC1.H1 (GND_9), IC1.H8 (GND_10), IC1.H9 (GND_11), IC1.H10 (GND_12), IC1.H16 (GND_13), IC1.J8 (GND_14), IC1.J9 (GND_15), IC1.J10 (GND_16), IC1.K6 (GND_17), IC1.K7 (GND_18), IC1.K8 (GND_19), IC1.K9 (GND_20), IC1.K10 (GND_21), IC1.N2 (GND_22), IC1.N15 (GND_23), IC1.T1 (GND_24), IC1.T5 (GND_25), IC1.T12 (GND_26), IC1.T16 (GND_27), IC1101.A9 (VSS_1), IC1101.B1 (VSSQ_1), IC1101.B3 (VSS_2), IC1101.B9 (VSSQ_2), IC1101.D1 (VSSQ_3), IC1101.D8 (VSSQ_4), IC1101.E1 (VSS_3), IC1101.E2 (VSSQ_5), IC1101.E8 (VSSQ_6), IC1101.F9 (VSSQ_7), IC1101.G1 (VSSQ_8), IC1101.G8 (VSS_4), IC1101.G9 (VSSQ_9), IC1101.J2 (VSS_5), IC1101.J8 (VSS_6), IC1101.M1 (VSS_7), IC1101.M9 (VSS_8), IC1101.P1 (VSS_9), IC1101.P9 (VSS_10), IC1101.T1 (VSS_11), IC1101.T9 (VSS_12), J201.1, J201.3, J201.5, J201.7, J201.9, J201.11, J701.1, J702.5 (GND), J702.11 (GND), J703.5 (GND), J703.11 (GND), J801.A1 (GND), J801.A12 (GND), J801.B1 (GND), J801.B12 (GND), J903.1, J903.5, J903.9, J1001.2 (Ext), J1002.2 (Ext), J1003.2 (Ext), J1004.2 (Ext), J1005.2 (Ext), J1006.2 (Ext), J1007.SH, J1008.2 (Ext), J1009.2 (Ext), J1010.2 (Ext), J1011.2 (Ext), J1201.10, J1201.S1 (SHIELD), J1201.S2 (SHIELD), JP1001.1 (A), JP1005.1 (A), JP1009.1 (A), JP1010.1 (A), L801.1, R204.2, R205.1, R206.2, R207.2, R212.1, R213.1, R216.1, R223.2, R224.1, R225.1, R227.2, R601.1, R603.1, R605.2, R607.2, R701.2, R704.2, R705.2, R707.1, R804.1, R805.1, R808.1, R810.2, R815.2, R818.1, R830.2, R1001.1, R1003.2, R1005.1, R1025.1, R1031.2, R1036.1, R1037.2, R1038.2, R1101.2, R1202.2, R1207.2, R1210.2, R1211.2, R1213.2, RJ1001.5, RJ1001.8 (GND), U201.3 (CP2), U201.6 (PR1), U201.12 (GND), U202.2 (GND), U203.2 (GND), U204.2 (GND), U205.2 (GND), U206.2 (V-), U701.4 (GND), U702.4 (GND), U801.1 (GND), U801.2 (GND), U801.33 (EPAD), U802.2 (V-), U803.2 (V-)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
unnamed: C806.2, R807.1, Y801.1
unnamed: C1012.1, R1016.2, U1002.4
unnamed: C1016.2, R1019.2, U1002.5
unnamed: C1017.1, J1007.8
unnamed: C1018.1, J1007.7
unnamed: C1028.1, J1007.1
unnamed: C1029.1, J1007.2
unnamed: C1228.2, R1201.1, Y1201.3
unnamed: D601.1 (K), R601.2
unnamed: D602.1 (K), R603.2
unnamed: D801.2 (A), R813.1
unnamed: D801.1 (K), R814.2, R815.1
unnamed: D802.2 (A), R821.1
unnamed: D802.1 (K), R826.2, R830.1
unnamed: C408.1, IC1.A7 (PT29A/PCLKT0_0), Y401.3 (OUT)
unnamed: IC1.E2 (PL8B/LDQSN8), R602.1
unnamed: IC1101.L8 (ZQ), R1101.1
unnamed: J1001.1 (In), R1006.2, R1007.1
unnamed: J1002.1 (In), R1010.2, R1011.2
unnamed: J1003.1 (In), R1008.2
unnamed: C1029.2, J1004.1 (In)
unnamed: J1005.1 (In), R1043.2
unnamed: J1006.1 (In), R1022.2, R1023.2
unnamed: J1008.1 (In), R1026.2, R1028.2
unnamed: J1009.1 (In), RJ1001.3
unnamed: J1010.1 (In), RJ1001.6
unnamed: C1028.2, J1011.1 (In)
unnamed: JP1001.2 (B), U1001.16 (TRISTATE), U1001.17 (STBY)
unnamed: Q201.3 (D), R203.1, U201.7 (IN1)
unnamed: Q201.1 (G), R206.1
unnamed: R219.2, R220.1, R221.2, R223.1
unnamed: R605.1, SW602.2
unnamed: R607.1, SW603.2
unnamed: R701.1, SW701.2
unnamed: R1001.2, RJ1001.13, RJ1001.14
unnamed: R1002.1, RJ1001.11
unnamed: R1004.1, RJ1001.10
unnamed: R1007.2, R1012.2, R1013.2
unnamed: R1009.1, R1016.1, R1017.1
unnamed: R1018.2, R1021.2, R1026.1
unnamed: R1019.1, R1020.1, R1024.2
unnamed: R1039.2, RJ1001.4
unnamed: R205.2, U201.10 (ILM)
unnamed: R203.2, R207.1, U201.5 (OV1)
unnamed: R226.2, R227.1, U201.4 (OV2)
unnamed: C202.1, U201.11 (SS)
unnamed: R204.1, U201.9 (ST)
unnamed: C203.2, R210.1, R212.2, U202.5 (FB)
unnamed: L201.1, U202.3 (SW)
unnamed: C228.1, R201.2, U203.1 (EN)
unnamed: C209.2, R211.1, R213.2, U203.5 (FB)
unnamed: L202.1, U203.3 (SW)
unnamed: C217.2, R215.1, R216.2, U204.5 (FB)
unnamed: L203.1, U204.3 (SW)
unnamed: C227.1, R202.2, U205.1 (EN)
unnamed: C219.2, R218.1, R225.2, U205.5 (FB)
unnamed: L204.1, U205.3 (SW)
unnamed: C226.1, R221.1, U206.3 (+)
unnamed: R222.2, R224.2, U206.1, U206.4 (-)
unnamed: R817.1, U801.14 (CLKOUT)
unnamed: R808.2, U801.32 (RBIAS)
unnamed: R801.2, U801.4 (VBUS)
unnamed: R806.1, R807.2, U801.28 (XI)
unnamed: C803.2, R806.2, U801.27 (XO), Y801.3
unnamed: C802.1, R816.1, R818.2, U802.1 (+)
unnamed: C817.1, R811.1, R812.2, U803.3 (+)
unnamed: R811.2, R813.2, U803.1 (OUT)
unnamed: C825.1, R802.2, R803.1, U804.3 (+)
unnamed: R803.2, R821.2, U804.1 (OUT)
unnamed: R1025.2, U1001.20 (CLAMPIN)
unnamed: C1016.1, R1021.1, R1024.1, U1002.8 (+)
unnamed: C1012.2, R1009.2, R1013.1, U1002.1 (-)
unnamed: R1015.2, U1002.7 (~PD)
unnamed: R1012.1, U1003.12 (COM1)
unnamed: R1018.1, U1003.16 (COM2)
unnamed: R1033.2, R1036.2, U1004.3 (-), U1004.4
unnamed: R1035.2, R1038.1, U1005.1 (REF)
unnamed: R1202.1, U1201.48 (ISET)
unnamed: C1227.2, U1201.46 (XI), Y1201.1
unnamed: R1201.2, U1201.45 (XO)
unnamed: R401.2, Y401.1 (Tri-State)
unnamed: C407.1, L401.2, R401.1, Y401.4 (VDD)
VCORE_3V3: C225.1, C301.1, C302.1, C303.1, C304.1, C305.1, C306.1, C307.1, C308.1, C309.1, C401.1, C402.1, C403.1, C404.1, C405.1, C406.1, C601.1, C602.1, C603.1, C611.1, C612.1, C613.1, C701.1, C702.1, C703.1, C704.1, C705.1, C706.1, C707.1, C809.1, C810.1, C811.1, C812.1, C813.1, C1007.1, C1008.1, C1221.1, C1222.1, C1223.1, C1224.1, C1225.1, D1201.1 (K), IC1.F6 (VCCIO0_1), IC1.F7 (VCCIO0_2), IC1.F10 (VCCIO1_1), IC1.F11 (VCCIO1_2), IC1.G6 (VCC_1), IC1.G7 (VCC_2), IC1.G9 (VCC_3), IC1.H6 (VCCIO7_1), IC1.H7 (VCCIO7_2), IC1.J6 (VCCIO6_1), IC1.J7 (VCCIO6_2), IC1.L6 (VCCIO8), IC1.L8 (VCC_4), IC1.L9 (VCC_5), IC1.L10 (VCC_6), J701.2, J702.6 (Vcc), J702.12 (Vcc), J703.6 (Vcc), J703.12 (Vcc), J1201.11, J1201.14, L401.1, L1001.1, L1203.1, R208.2, R604.1, R606.1, R706.1, R1203.1, R1204.2, R1205.2, R1208.2, R1212.2, RN703.6 (R3.2), RN703.7 (R2.2), RN703.8 (R1.2), RN704.5 (R4.2), RN704.6 (R3.2), RN704.7 (R2.2), RN704.8 (R1.2), RN707.5 (R4.2), RN707.6 (R3.2), RN707.7 (R2.2), RN707.8 (R1.2), RN708.5 (R4.2), RN708.6 (R3.2), RN708.8 (R1.2), RN1201.5 (R4.2), RN1201.6 (R3.2), RN1201.7 (R2.2), RN1201.8 (R1.2), TP205.1, U206.5 (V+), U701.8 (VCC), U702.8 (VCC), U801.6 (VDD3.3), U801.16 (VDD3.3), U801.25 (VDD3.3), U801.30 (VDD3.3), U801.31 (REG_EN), U1001.2 (DRVDD), U1201.16 (DVDDH), U1201.34 (DVDDH), U1201.40 (DVDDH)
VDDA: C1005.1, C1006.1, C1019.1, C1021.1, C1023.1, C1024.1, C1025.1, JP1003.1 (A), JP1006.1 (A), L1001.2, R1015.1, R1030.1, R1032.1, R1034.1, RJ1001.9, RJ1001.12, TP1001.1, U1001.28 (AVDD), U1002.3 (V_{S+}), U1003.10 (V+), U1004.5 (V+)
VETH_1V2: C1213.1, C1214.1, C1215.1, C1216.1, C1217.1, C1218.1, C1219.1, C1220.1, L1201.2, L1202.2, R209.2, TP206.1, U1201.14 (DVDDL), U1201.18 (DVDDL), U1201.23 (DVDDL), U1201.26 (DVDDL), U1201.30 (DVDDL), U1201.39 (DVDDL)
VLPDDR3_1V35: C501.1, C502.1, C503.1, C509.1, C510.1, C511.1, C512.1, IC1.H11 (VCCIO2_1), IC1.J11 (VCCIO2_2), IC1.K11 (VCCIO3_1), IC1.L11 (VCCIO3_2), L1101.2, L1102.2, R217.2, R219.1, TP209.1
VLPDDR3_V675: C507.1, C508.1, C513.1, C1114.1, C1115.1, C1121.1, C1122.1, IC1.G14 (PR14C/VREF1_2), IC1.R16 (PR35B/VREF1_3), IC1101.H1 (VREFDQ), IC1101.M8 (VREFCA), R220.2, R222.1, TP208.1
~ETH_INT: IC1.E1 (PL11D/LDQ8), R1208.1, U1201.38 (INT_N/PME_N2)
~ETH_RESET: C1229.1, D1201.2 (A), R602.2, R1212.1, U1201.42 (RESET_N)

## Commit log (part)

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2025-04-27 [simulations] Added vishay FET to inverter bridge + connected Vs [documentation] Redid driving circuitry calculation [next] Spot a decent ADC
2025-04-27 [simulations] Updated sim with new values [kicad] Added inverter circuitry to schematic, add bulk capacitor LCSC parts, add pads for power connections.
2025-04-28 [kicad] Added capacitors, [documentation] Added bootstrap + HF frequency capacitor calculations
2025-04-29 [kicad] Added analog front-end schematic and MS9280 symbol
2025-04-29 [documentation, kicad] Added decoupling capacitors + input circuitry for adc (next) Look for a decent connector
2025-04-30 [documentation] Researched output power connectors and input connectors (next) select appropriate terminal and rj45 connector
2025-05-01 [kicad] Added connector + input circuit (next) Simulate adc input circuit in ltspice
2025-05-01 [simulations] Finished full adc input stage simulation
2025-05-02 [documentation] Added info on example circuits used, worked on filtering and FPGA info
2025-05-02 [VHDL]added VHDL folder
2025-05-03 [simulations] Added comments concerning differential vs single-ended filtering
2025-05-03 [VHDL] Added initial verilog examples + extra FPGA choices
2025-05-03 [VHDL, lit3rick example] Finished going over example vhdl
2025-05-04 [VHDL] (examples) Went over examples to check global data-flow
2025-05-04 [documentation] Minor changes in docs
2025-05-04 [kicad] Added flash memory + flash connection (next) Add RAM and ethernet
2025-05-06 [kicad] Connected DDR3L bus, added info on FPGA and ddr pin functionality (next) add filtering circuitry for DDR power pins
2025-05-06 [kicad] re-added passive values after accidental removal
2025-05-06 [simulations] Added 3 buck converter simulations (next) Add fast-switching 13 V buck converter simulation + try improving the switching regulator characteristics with extra 10 uF cap
2025-05-06 [kicad] Added switching regulators for 3.3, 1.25 and 2.5
2025-05-07 [general] Major repo reorganization, separated into carrier-board, power-board, preamp-board
2025-05-07 test
2025-05-08 [carrier] Same as previous [piezodriver] Moved inverter to separate board
2025-05-08 [carrier] Added decoupling for DDR (next) Finish power supply
2025-05-08 added decoupling and power flags
2025-05-09 [carrier] Added space for ferrite bead in between bulk and decoupling caps
2025-05-10 [carrier] Finished ethernet
2025-05-10 [carrier] Added usb power + communication circuitry (next) Connect ADC pins to bank 0, select PWM pins, check connectors for power board
2025-05-11 [carrier] Added adc connections and PWM + poweer connectors
2025-05-11 [piezodriver] Added piezo-driver board connectors
2025-05-12 [piezo-driver] Doing boost converter simulations (next) fix weird transient, add buck-converter simulations for 10 and 5 V
2025-05-13 [piezodriver] Fixed the basic boost converter simualtion
2025-05-14 [piezodriver] (simulations) figured minimum driving voltage for FET is > 4 V (next) Add Sepic, check behavior > 7.2 V
2025-05-14 [piezodriver] Selection of diode and fet (next) do SEPIC calculations
2025-05-18 [piezodriver] Added notes on sepic calculation
2025-05-18 [piezodriver] Did analysis of SEPIC, went over inherent duty cycle limits, losses, slope compensation, sense resistor and peak current control
2025-05-18 [piezodriver] (ltspice) Added dead-time to full-bridge
2025-05-18 [piezodriver] Added X7R input capacitor, add input and output capacitance of 40-100 uF
2025-05-19 [piezodriver] Finished 2 sepic designs, starting boost design (warn) Make sure to max diode voltage difference
2025-05-19 [piezodriver] Choose smaller inductor with larger current carrying capacity, increase switching frequency (but check LM3478 limits)
2025-05-20 [piezodriver] Finished boost converter dynamics, added compensation circuitry
2025-05-20 [carrier] Reordered carrier board (next) add magnetics to adc differential and ethernet instead of capacitors - SRF is too low
2025-05-23 [carrier] Research on piezo-element
2025-05-24 [carrier] Added second adc input with magnetics, added ethernet connector with magnetics [piezodriver] Added diodes to level shifters for gate charge return current
2025-05-24 [carrier] Started schematic check, replaced 8 with 16 pin connectors
2025-05-25 [carrier] removed external led, using ethernet leds, replaced 1kOhm by 470 ohm resistors
2025-05-25 [carrier] Fixed ERC errors and fpga-footprints (next) ) add extra pin functionality to 2 remaining banks, perform schematic checks
2025-05-26 [carrier] added rudimentary LC filter at input (next) - provision signal generator input
2025-05-29 [carrier] Updated requirements for ADC (next) check if you can make the ADC single-ended, add a buffer amplifier
2025-05-29 [carrier] Chose amplifier, changed adc voltage range (next) change commmon mode source, add decoupling, add buffering to common mode
2025-05-31 [carrier] Started tina simulations with th4521
2025-05-31 [carrier] Added adc input stage simulation with tina-ti and th4521 (next) add similar common-mode simulation for verification
2025-06-01 [carrier] Added full simulation with VOCM amplification
2025-06-01 [carrier] Added buffered VOCM (next) add switch on which was decided, add biasing after ac coupling caps, add provisionary pull-ups at of THS452 INPUT-
2025-06-02 [carrier] Replaced voltage reference, added extra 0 ohm resistors, added test-connectors for ADC testing
2025-06-02 [carrier] Added full pin description to BGA symbol
2025-06-02 [carrier] Added 100 MHz crystal oscillator (next) Do a component / footprint check
2025-06-02 [carrier] Fixed minor symbol errors, added minor routing info (next) continue schematic check
2025-06-03 [carrier] Did additional tests with tina-ti and blocking cap, did schematic check up to adc input buffer
2025-06-03 [carrier] analog frontend check DONE, (next) check config and boot-flash pin connections
2025-06-03 [piezodriver] Added tina-ti simulation of 10V sepic (next) fix this sim, add power circuitry sim for carrier in tina-ti
2025-06-04 [carrier] Further verification of power board (next) Replace ddr3l reference voltage using TPS51200
2025-06-04 [carrier] Checked power-supply part (next) check ethernet-board
2025-06-04 [carrier] Checked ethernet decoupling + pins + pad + resonator
2025-06-05 [carrier] Added separate buses for ddr3 ctrl-cmd and dq-groups
2025-06-06 [carrier] Worked on USB connector
2025-06-08 [carrier] Finished schmitt trigger for cc1 and cc2 led driver + passive power signalling
2025-06-08 [carrier] Added schmitt trigger for switch (next) check if well-connected (polarity)
2025-06-10 [carrier] Fixed error in ethernet power supply, separated footprints + symbols into library (next) check whether supply should be DVDDH
2025-06-10 removed kicad-magic
2025-06-10 [¢arrier] Removed individual footprints and symbols
2025-06-10 [carrier] Finished switch and reverse voltage circuit
2025-06-11 [¢arrier] Fixed busses, added resistive arrays instead of 4x4k7 or 4x10k
2025-06-11 [carrier] Added separate schematics for banks
2025-06-11 [carrier] Added decoupling caps to flash and comparators
2025-06-11 [carrier] Added extra decoupling to ECP5U according to datasheet (next) perform page-wise checks, add testpoints
2025-06-12 [¢arrier] Finished checks, startting with layout and routing
2025-06-12 [¢arrier] Checked stackup theory, return current theory (next) continue researching ideal stackup
2025-06-15 [carrier] Added testpoints
2025-06-17 [carrier] Finished rough layout, p (put together according to component category
2025-06-17 [¢arrier] Added netties and determined trace geometry for 50 ohms SE / 100 ohms DIFF impedance (next) reset the appropriate DQS group signals, RGMII and USB signals
2025-06-19 [carrier] Removed USB-switch, placed decouplpling for DDR3 and ECP5U (next) consider adding buffers on CC1 and CC2 pins
2025-06-20 [carrier] connected ethernet, usb and adc to appropriate banks, redpositioned schmitt trigger and USB
2025-06-20 [¢arrier] Placed decoupling for some banks, placed dc-dc converterss (next) switch dc-dc converter pins around, switch adc-inputs around
2025-06-21 [¢arrier] Placed power supply circuitry appropraitely, changed power connector (next) Place schmitt triggers between usb and power, put critical circuitry closer together, place config circuitry
2025-06-21 [carrier] Layout more or less complete (next) think about adding 6x2 connectors, and add extra pin signals to the connector for testing
2025-06-21 [carrier] trying horizontal layout
2025-06-21 [carrier] Horizontal DDR3 orientation
2025-06-22 [carrier] Routed LDQ group and CMD-CTRL bus
2025-06-22 [carrier] Connected part of DQU
2025-06-22 [carrier] Routing out RGMII interface
2025-06-25 Did big ig parts of routing (next) make sure to re-add pull-ups/downs accordingly
2025-06-26 [carrier] Redid routing to PMOD SPI-flash ah (next) add second PMOD-connector and third connector meant for PWM signalling to power board
2025-06-27 [carrier] Routed 6x2 IO connector
2025-06-27 [carrier] Progressing on ddr3 routing (next) check all ddr3 signals for errors, start length matching
2025-06-27 [carrier] Matched address bus to 60 mm (nextt) match dq groups to 60 mm
2025-06-28 [carrier] rerouted USB ULP traces (next) add power planes
2025-06-29 [carrier] Starting on power planes
2025-06-29 [carrier] Drew all main planes (next) go sheet by sheet connecting decoupling where necessary and drawing reference signals on power plane
2025-06-30 [carrier] Changed all vias to (pcheaper) 0.2/0.35 size (next) create basic test-VHDL for clock-signal fanout checks
2025-07-02 [carrier] Rerouted USB-clock, checked setupp and hold conditions, length-matched ULPI
2025-07-02 [carrier] Started writing constraints file for ECP5U-FPGA (next) finish constraints file, try basic synthesis with pins and hello-world
2025-07-04 [carrier] Added rgmii example code, ulpi testcode synthesising, adding verilator code for compilation
2025-07-05 [carrier] Dummy ddr3 clock peripheral added
2025-07-06 [carrier] Attempting to place and route vhdl verification code (next) move everything to separate VHDL repo
2025-07-06 [carrier] Moved vhdl into separate repo
2025-07-08 [carrier] Added decoupling to LPDDR3 and routed VREF (next) finalize power supply
2025-07-08 [carrier] Further routing, ground plane removal underneath connectors, ..
2025-07-10 [carrier] Added delayed startup + some traces (next) fix the errors inside the DDR3 routing somehow
2025-07-11 [carrier] DRC fixes
2025-07-13 [carrier] Fixed most routing errors
2025-07-13 [carrier] Fixed drc errors (next) do final checks (including length checks on clk)
2025-07-14 [carrier] Added return vias for LPDDR3, analog, USB and Gb-Eth. Added GND via arrays between power-converters, analog and digital for isolation
2025-07-14 [carrier] Redrew isolation traces for switching power / analog / digital
2025-07-15 [carrier] posted to reddit
2025-07-16 [carrier] added silkscreen, moved lpddr3 traces around slightly
2025-07-17 [piezodriver] Reorganised piezodriver schematic (next) figure out output filtering
2025-07-17 [carrier] minor changes and checks
2025-07-21 [carrier] did initial ddr3 delay calculation (next) verify lengths, check allowed offset between DQs and CK, convert to lengths
2025-07-22 [carrier] Minor changes in routing documentation
2025-07-23 [carrier] todo: recalculate validity window
2025-07-24 [carrier] Added testpoints to lpddr3 (next) do final checks before ordering
2025-07-26 [carrier] finished for production (next) reroute the LPDDR3, with appropriate CMD-CTRL bus delays, and change banks for command-control
2025-07-27 [carrier] Finished routing, layed out lpddr3 capacitors (next) route power on plane
2025-07-28 [carrier] Added more return vias (next) move to separate repo
2025-07-28 [acoustic-processing-board] Added board as submodule
2025-07-28 [piezodriver] Added piezodriver as module
2025-07-28 [preamp] Removed preamp-hw
2025-07-28 [processing] Changed acoustic-processing-board->hw repo name
2025-07-29 Diagram creation, submodules updated
2025-07-31 sync
2025-08-07 modified readme (next) complete drawio diagram, finish documentation
2025-08-31 added case dimensions
2025-08-31 finished bottom case basics (next) make holes for connectors and pinheaders, make top lid
2025-09-18 addedtestcode to piezodriver
2025-09-29 added notes on bringup (next) try pinpointing the location by zooming into short
2025-10-25 case updates
2025-10-25 removed preamp repo, wasn't used in v1
2025-10-25 updated v2 to latest version
